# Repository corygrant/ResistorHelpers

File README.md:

# ResistorHelpers
Small resistor PCBs for wiring, with notches for cable ties. 

- Resistor Divider

- Resistor Pullup

- Terminating Resistor

- Inline Resistor

# Images

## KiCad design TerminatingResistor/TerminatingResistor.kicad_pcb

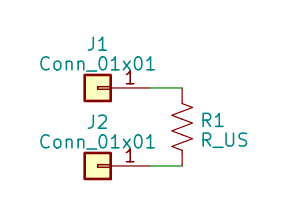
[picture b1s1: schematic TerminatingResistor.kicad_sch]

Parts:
J1, J2: Conn_01x01; SolderWire-0.5sqmm_1x01_D0.9mm_OD2.1mm
R1: R_US; R_0805_2012Metric

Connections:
unnamed: J1.1, R1.1
unnamed: J2.1, R1.2

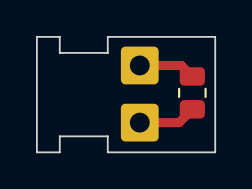
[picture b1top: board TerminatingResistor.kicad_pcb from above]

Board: 2 copper layers, 9.9 x 6.4 mm, 3 parts (0 on the bottom side), 2 nets.

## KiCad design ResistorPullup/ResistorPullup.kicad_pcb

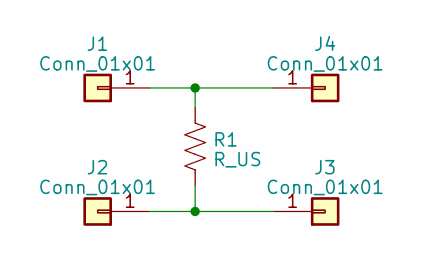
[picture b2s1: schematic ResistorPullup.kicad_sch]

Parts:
J1, J2, J3, J4: Conn_01x01; SolderWire-0.5sqmm_1x01_D0.9mm_OD2.1mm
R1: R_US; R_0805_2012Metric

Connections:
unnamed: J1.1, J4.1, R1.1
unnamed: J2.1, J3.1, R1.2

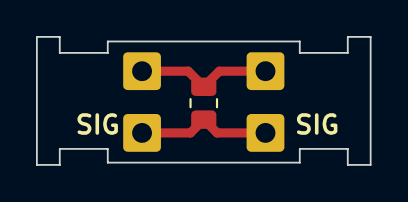
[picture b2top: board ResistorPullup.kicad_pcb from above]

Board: 2 copper layers, 18.5 x 7.1 mm, 5 parts (0 on the bottom side), 2 nets.

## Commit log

2023-05-04 As ordered
2023-05-04 Added images
2023-08-11 Change LICENSE.MD
2024-09-06 Update to Kicad 8
